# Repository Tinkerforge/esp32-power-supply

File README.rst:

ESP32 Power Supply
==================

This repository contains the firmware source code and the hardware design
files. The documentation generator configs can be found at
https://github.com/Tinkerforge/generators

Repository Content
------------------

software/:
 * examples/: Examples for all supported languages
 * build/: Compiled files
 * src/: Source code of firmware
 * Makefile: Makefile to build project

hardware/:
 * Contains KiCad project files and additionally schematics as PDF

datasheets/:
 * Contains datasheets for sensors and complex ICs that are used

Hardware
--------

The hardware is designed with the open source EDA Suite KiCad
(http://www.kicad.org). Before you are able to open the files,
you have to install the Tinkerforge kicad-libraries
(https://github.com/Tinkerforge/kicad-libraries). You can either clone
them directly in hardware/ or clone them in a separate folder and
symlink them into hardware/
(ln -s kicad_path/kicad-libraries project_path/hardware). After that you
can open the .pro file in hardware/ with KiCad and from there view and
modify the schematics and the PCB layout.

Software
--------

If you want to do your own Brick/Bricklet firmware development we highly
recommend that you use our build environment setup script and read the
tutorial (https://www.tinkerforge.com/en/doc/Tutorials/Tutorial_Build_Environment/Tutorial.html).

To compile the C code we recommend you to install the newest GNU Arm Embedded
Toolchain (https://launchpad.net/gcc-arm-embedded/+download).
You also need to install bricklib (https://github.com/Tinkerforge/bricklib).

You can either clone it directly in software/src/ or clone it in a
separate folder and symlink it into software/src/
(ln -s bricklib_path/bricklib project_path/software/src/). Finally make sure to
have CMake installed (http://www.cmake.org/cmake/resources/software.html).

After that you can build the firmware by invoking make in software/.
The firmware (.bin) can then be found in software/build/ and uploaded
with brickv (click button "Flashing" on start screen).

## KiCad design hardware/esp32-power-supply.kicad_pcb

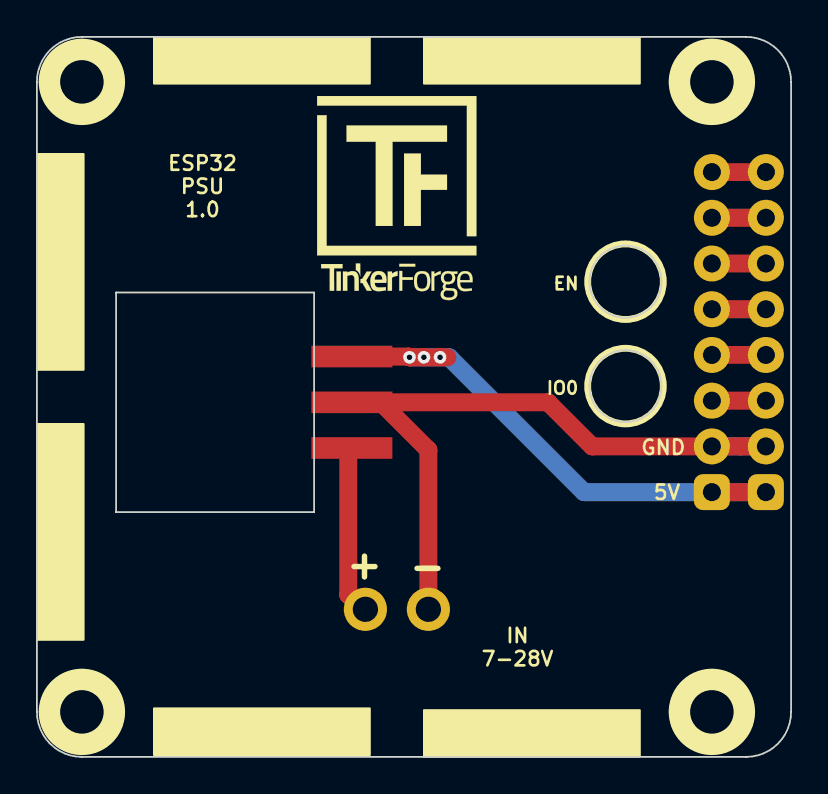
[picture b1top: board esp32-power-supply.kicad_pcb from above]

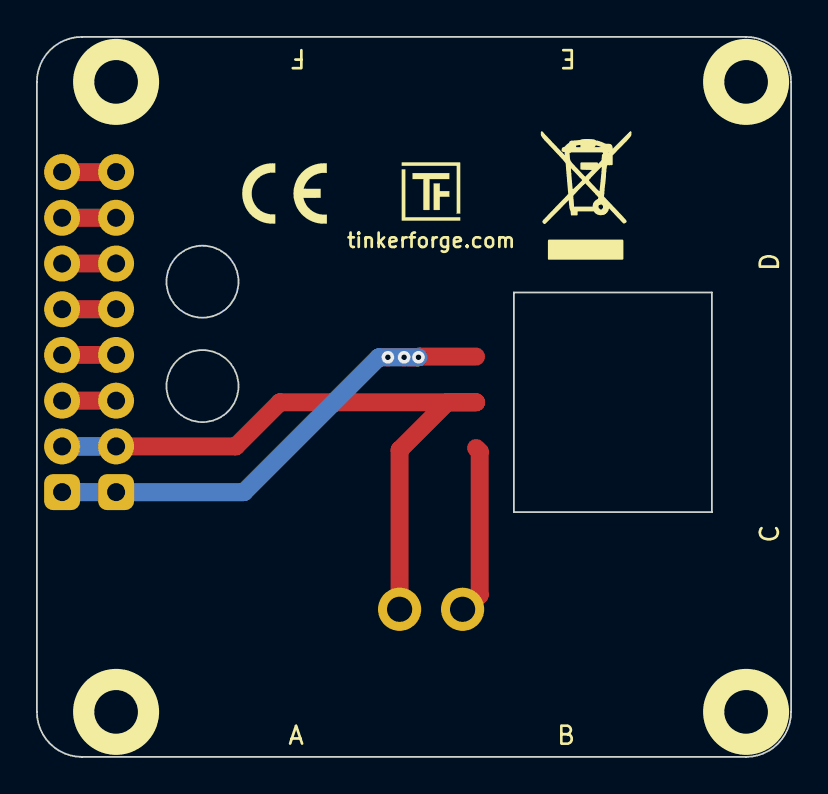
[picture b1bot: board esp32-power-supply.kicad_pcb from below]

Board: 2 copper layers, 41.9 x 40.0 mm, 10 parts (2 on the bottom side), 9 nets.

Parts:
F101, F102, F103, F104: DRILL; DRILL_NP
P1: CONN_01X02; OQ_2P
P2, P101: EXT_HEADER; pin_array_1x8-P2mm_D1mm
U1: WPMDL110; WPMDL110_side
VAL: WEEE_7mm
VAL#2: CE_5mm

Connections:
IN_7-28V: P1.1, U1.1
unnamed: P1.2, P2.2, P101.2, U1.2
unnamed: P2.3, P101.3
unnamed: P2.4, P101.4
unnamed: P2.5, P101.5
unnamed: P2.6, P101.6
unnamed: P2.7, P101.7
unnamed: P2.8, P101.8
OUT_5V: P2.1, P101.1, U1.3

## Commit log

2022-04-01 initial checkin
2022-04-01 add 3d file
2022-04-01 fix 3d path
2022-09-09 add 3d data

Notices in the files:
hardware/esp32-power-supply.kicad_pcb:
Licensed under CERN OHL v.1.1
Copyright (©) 2021, B.Nordmeyer
Copyright Tinkerforge GmbH 2021.
This documentation describes Open Hardware and is licensed under the
CERN OHL v. 1.1.
